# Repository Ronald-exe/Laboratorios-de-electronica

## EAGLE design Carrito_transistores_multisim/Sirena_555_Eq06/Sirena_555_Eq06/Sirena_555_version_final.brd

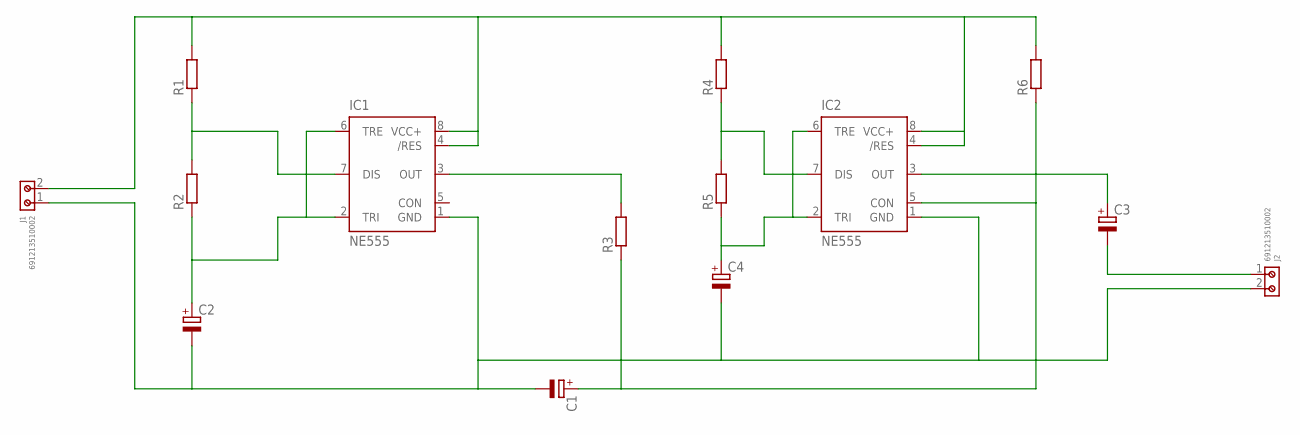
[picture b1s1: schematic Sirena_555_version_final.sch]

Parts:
C1: CPOL-EUE3.5-10; E3,5-10
C2, C3: CPOL-EUE2.5-5; E2,5-5
C4: CPOL-EUE2-4; E2-4
IC1, IC2: NE555; DIL-08
J1, J2: 691213510002
R1, R2, R3, R4, R5, R6: R-EU_0309/12; 0309/12

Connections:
GROUND: C1.-, C2.-, C4.-, IC1.1 (GND), IC2.1 (GND), J1.1, J2.2
unnamed: IC1.4 (/RES), IC1.8 (VCC+), IC2.4 (/RES), IC2.8 (VCC+), J1.2, R1.2, R4.2, R6.2
unnamed: IC1.7 (DIS), R1.1, R2.2
unnamed: C2.+, IC1.2 (TRI), IC1.6 (TRE), R2.1
unnamed: C4.+, IC2.2 (TRI), IC2.6 (TRE), R5.1
unnamed: IC1.3 (OUT), R3.2
unnamed: C1.+, IC2.5 (CON), R3.1, R6.1
unnamed: C3.-, J2.1
unnamed: IC2.7 (DIS), R4.1, R5.2
unnamed: C3.+, IC2.3 (OUT)

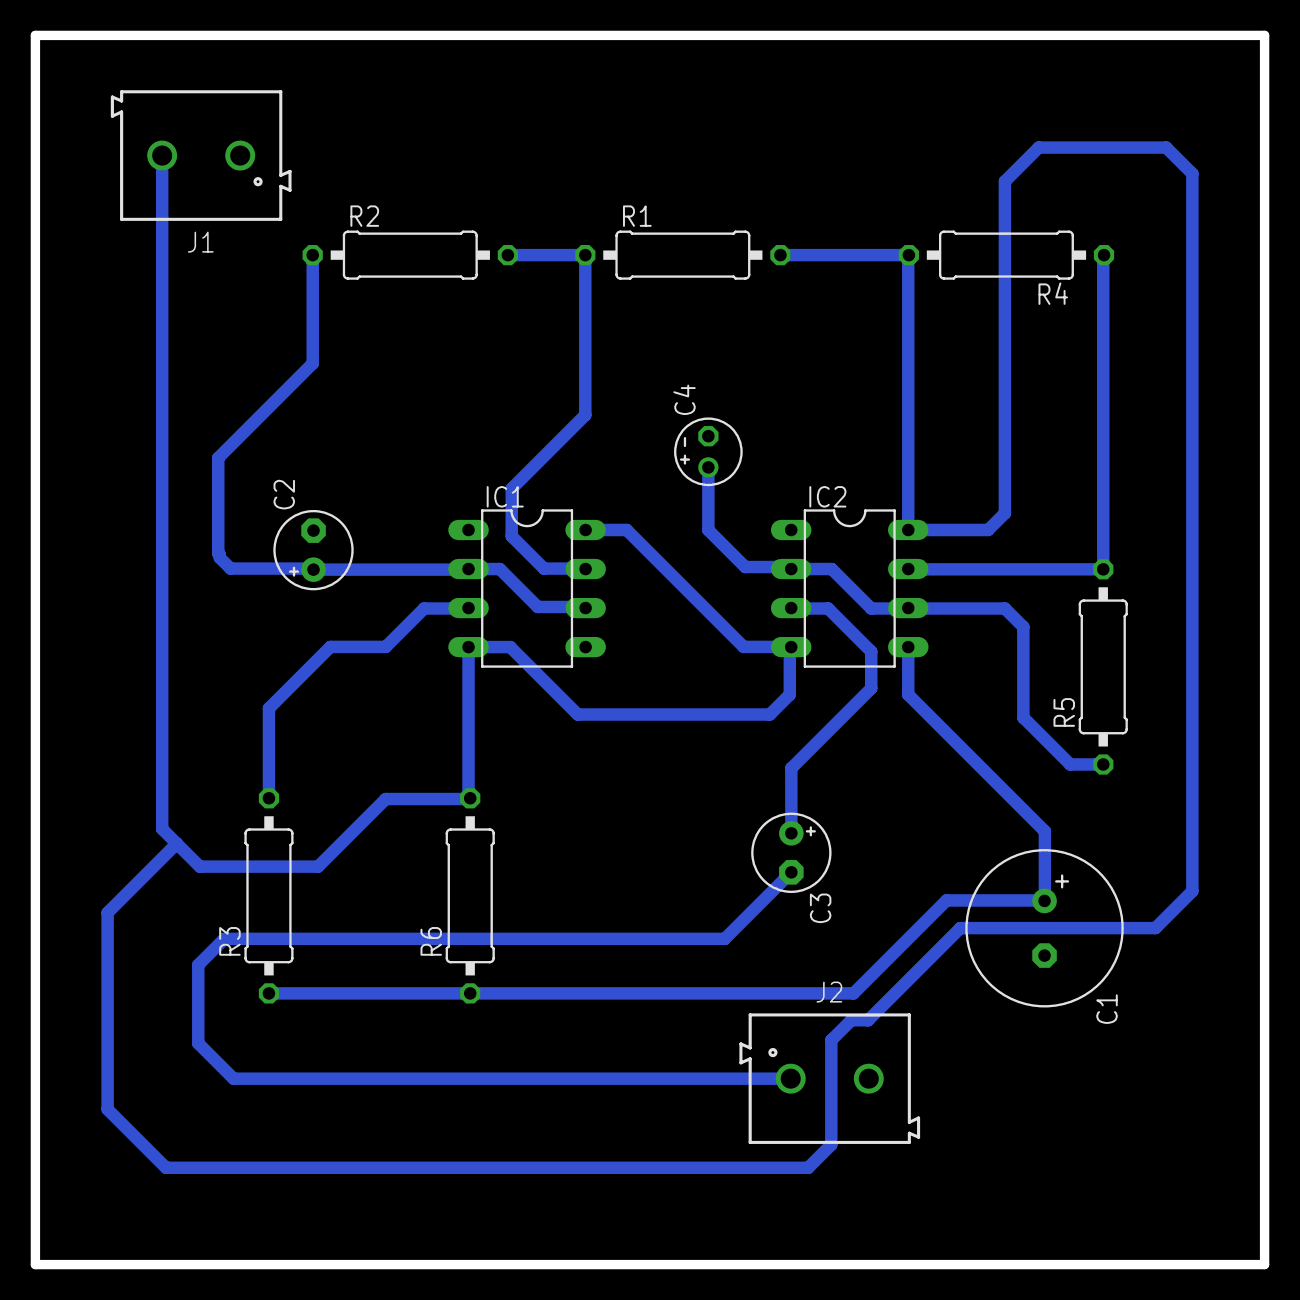
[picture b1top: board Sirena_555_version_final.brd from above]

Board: 2 copper layers, 80.0 x 80.0 mm, 14 parts (0 on the bottom side), 10 nets.

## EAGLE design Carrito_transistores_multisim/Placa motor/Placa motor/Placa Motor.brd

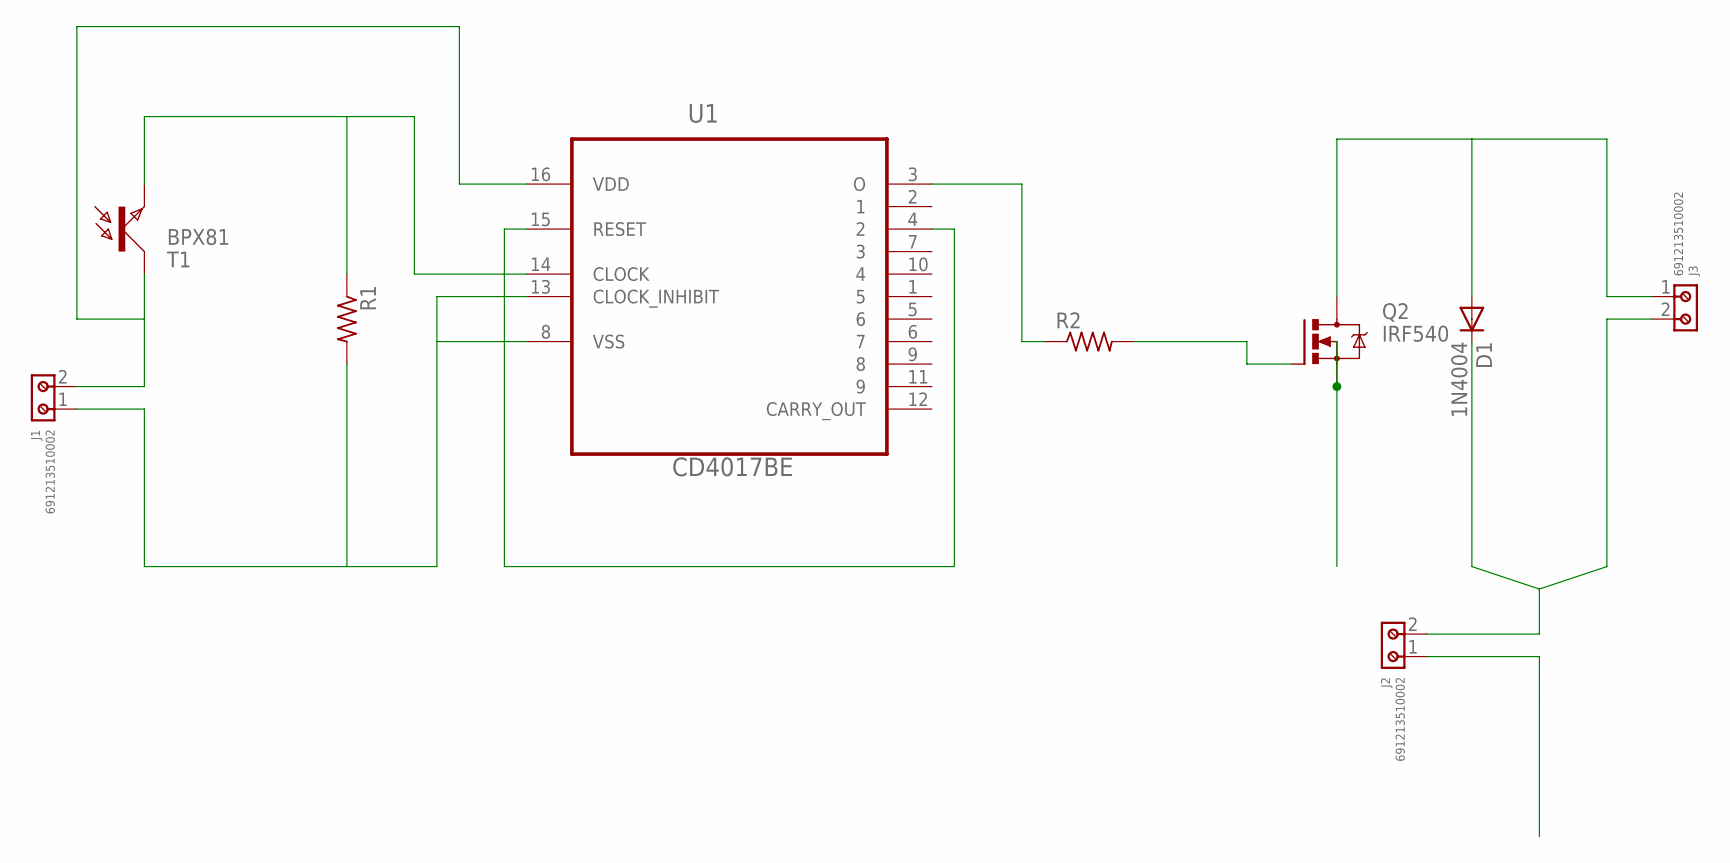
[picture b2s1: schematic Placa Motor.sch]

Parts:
D1: 1N4004; DO41-10
J1, J2, J3: 691213510002
Q2: IRF540; TO220BV
R1, R2: R-US_0309/12; 0309/12
T1: BPX81
U1: CD4017BE; DIP254P762X508-16

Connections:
GROUND: J1.1, J2.1, Q2.S, R1.2, U1.8 (VSS), U1.13 (CLOCK_INHIBIT)
unnamed: J1.2, T1.C, U1.16 (VDD)
unnamed: R1.1, T1.E, U1.14 (CLOCK)
unnamed: U1.4 (2), U1.15 (RESET)
unnamed: D1.A, J3.1, Q2.D
unnamed: D1.C, J2.2, J3.2
unnamed: R2.1, U1.3 (O)
unnamed: Q2.G, R2.2

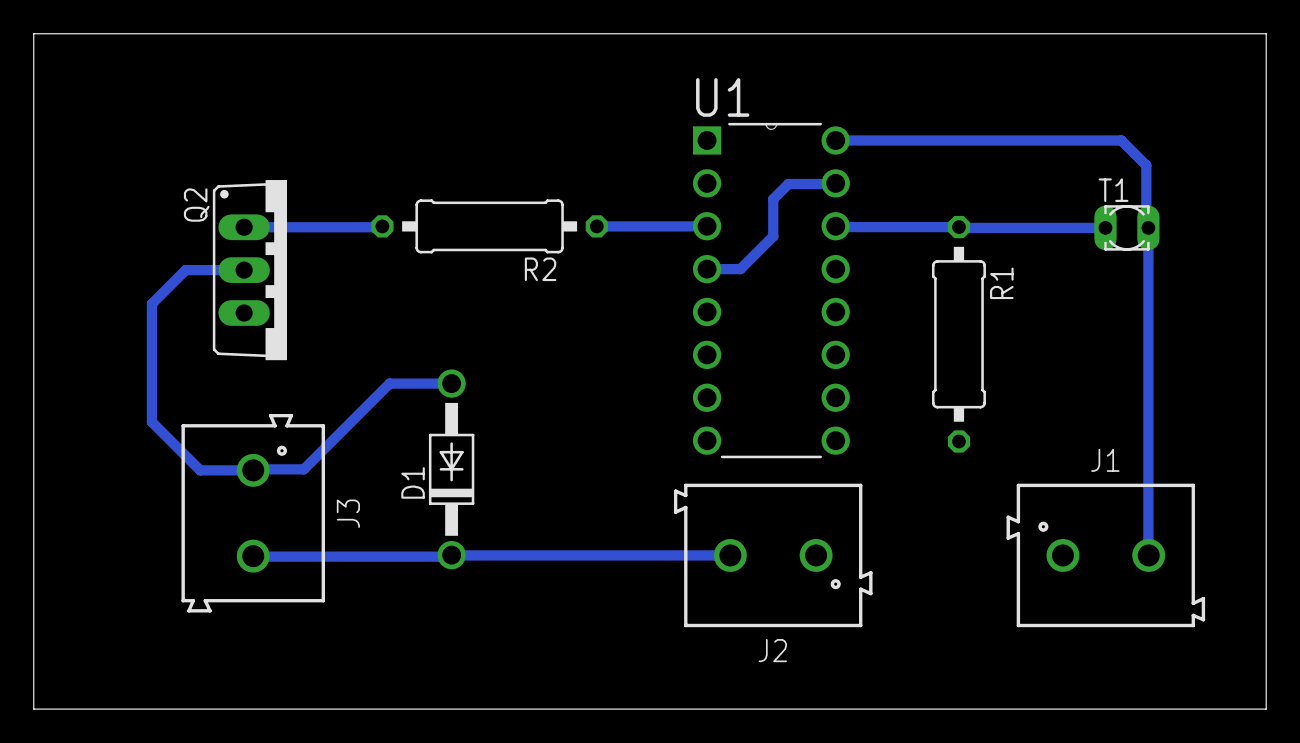
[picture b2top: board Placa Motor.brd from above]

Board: 2 copper layers, 73.0 x 40.0 mm, 9 parts (0 on the bottom side), 8 nets.

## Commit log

2026-01-09 Update_multisim_lab
2026-01-09 cambio informe
